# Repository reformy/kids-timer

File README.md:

# kids-timer

A timer for my kids, capable of counting 1 to 99 minutes. I am sick of saying "I said 20 minutes on the computer!"...

This project uses SevSeg https://github.com/DeanIsMe/SevSeg.

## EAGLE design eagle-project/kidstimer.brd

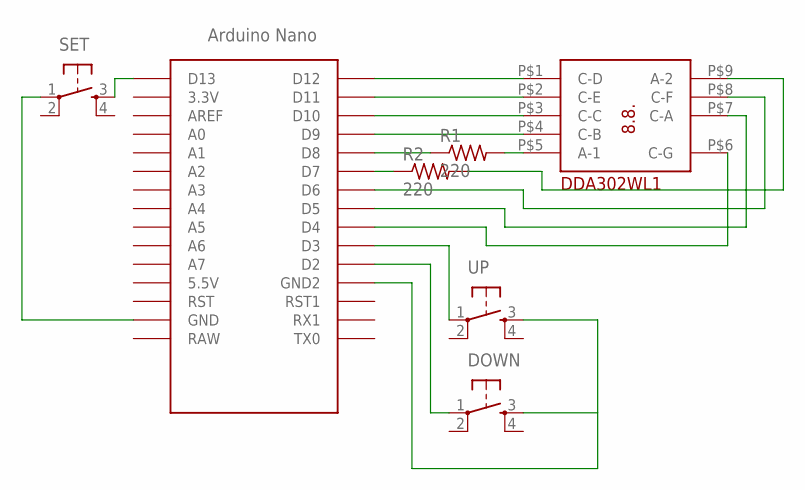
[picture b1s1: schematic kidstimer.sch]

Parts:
DOWN: TAC_SWITCHPTH; TACTILE-PTH
R1, R2: 220; 0207/10
SET: TAC_SWITCHPTH; TACTILE-PTH
U$1: DDA302WL1DIP9; DIP9
U$2: NANO
UP: TAC_SWITCHPTH; TACTILE-PTH

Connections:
unnamed: U$1.P$1 (C-D), U$2.D12
unnamed: U$1.P$2 (C-E), U$2.D11
unnamed: U$1.P$3 (C-C), U$2.D10
unnamed: U$1.P$4 (C-B), U$2.D9
unnamed: R1.2, U$1.P$5 (A-1)
unnamed: U$1.P$6 (C-G), U$2.D4
unnamed: U$1.P$7 (C-A), U$2.D5
unnamed: U$1.P$8 (C-F), U$2.D6
unnamed: R2.2, U$1.P$9 (A-2)
unnamed: R2.1, U$2.D7
unnamed: R1.1, U$2.D8
unnamed: U$2.D3, UP.1
unnamed: SET.1, U$2.GND
unnamed: DOWN.1, U$2.D2
unnamed: SET.3, U$2.D13
unnamed: DOWN.3, U$2.GND1 (GND2), UP.3

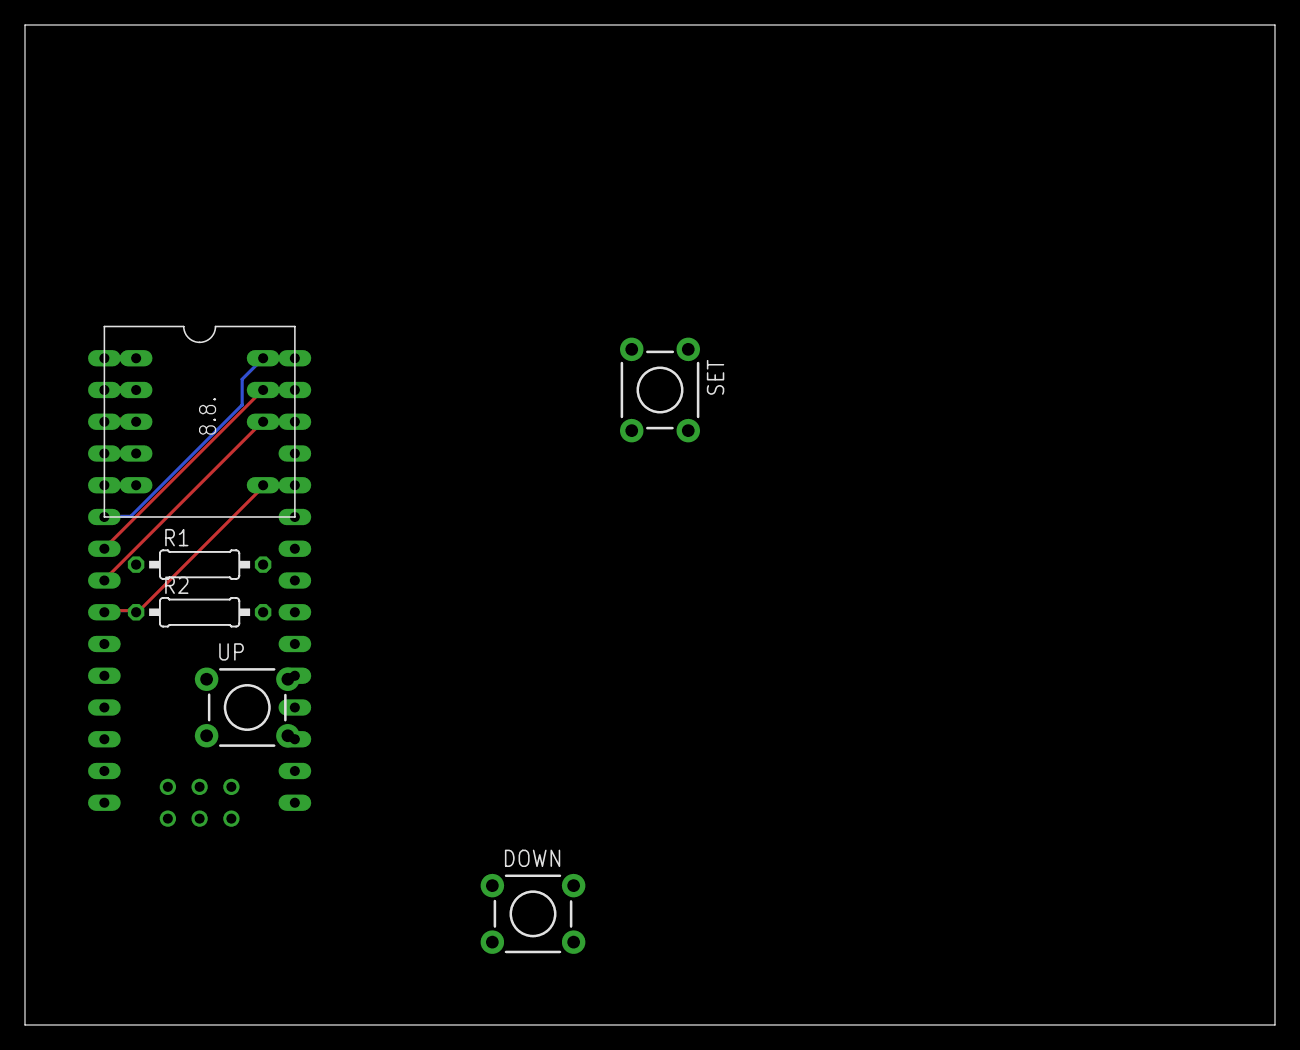
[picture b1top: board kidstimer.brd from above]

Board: 2 copper layers, 100.0 x 80.0 mm, 7 parts (1 on the bottom side), 16 nets.

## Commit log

2016-10-08 Added eagle scatch. Created arduino project.
2016-10-08 First try of the SevSeg library.
2016-10-08 Showing seconds! nice.
2016-10-08 First try with up down - not working.
2016-10-09 Working timer!
2016-10-12 Changed pins after soldering

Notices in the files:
parts and their libraries:
SparkFun-Retired: Licensing:Creative Commons ShareAlike 4.0 International - https://creativecommons.org/licenses/by-sa/4.0
